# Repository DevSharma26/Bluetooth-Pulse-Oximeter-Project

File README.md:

# EDW-Project
This project is our first ever foray into the world of practical electronics and an attempt to create a working device, Pulse Oximeter (in this case).
All the required info about the components, project specific details plus a beginner's overview is documented in the "project proposal" doc.
The various pointers and our fixes to some common problems are present in the "project documentation".
Also included are the arduino code, the eagle schematic and eagle board layout for the pcb.
This repo contains every piece of info and documentation that we deemed relevant for a third person to understand the motives behind the project and replicate it with elementary knowledge of electronics and pcb fabricating.
However, if any problem is encountered in the project try to troubleshoot using google and/or helpful friends/teachers/professors like we did 
happy bulding!!

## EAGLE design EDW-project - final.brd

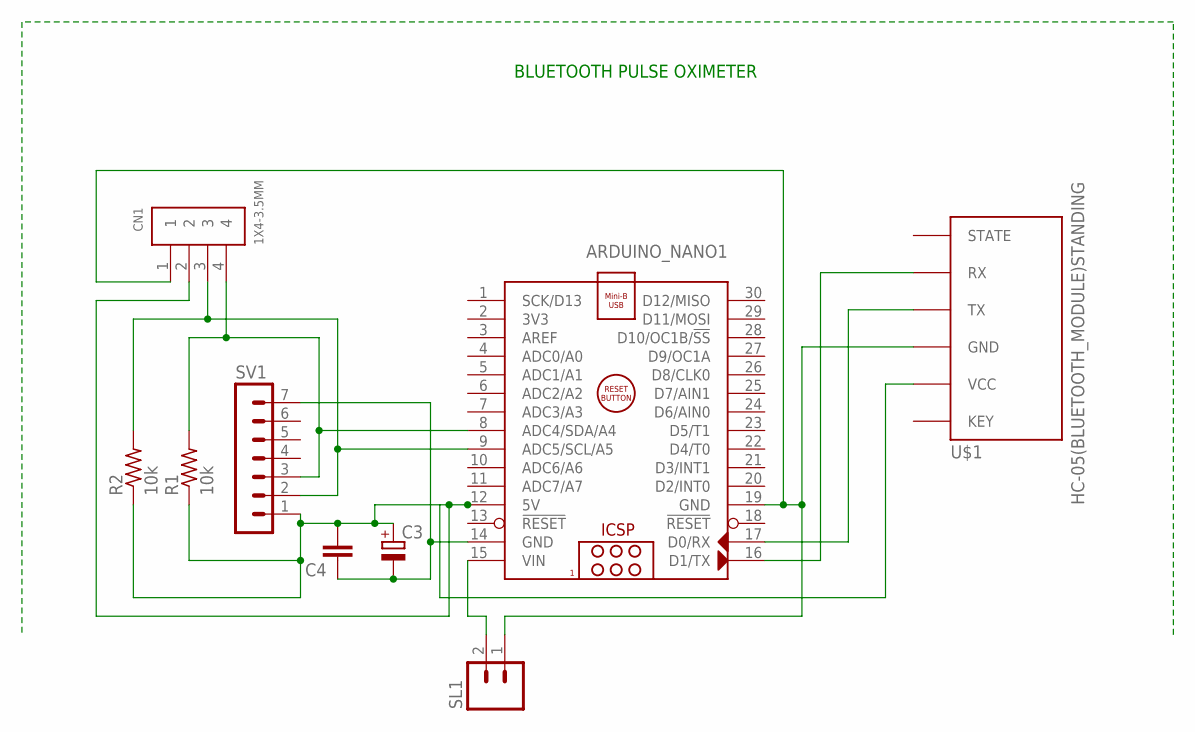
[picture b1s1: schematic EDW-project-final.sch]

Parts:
ARDUINO_NANO1: ARDUINO_NANO
C3: CPOL-EUE2.5-6; E2,5-6
C4: C-EU025-024X044; C025-024X044
CN1: 1X4-3.5MM; 1X04-3.5MM
R1, R2: 10k; 0207/7
SL1: M02; 02P
SV1: MA07-1
U$1: HC-05(BLUETOOTH_MODULE)STANDING; HC-05(STANDING)

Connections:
unnamed: ARDUINO_NANO1.8 (ADC4/SDA/A4), CN1.4, R1.2, SV1.3
unnamed: ARDUINO_NANO1.15 (VIN), SL1.2
unnamed: ARDUINO_NANO1.16 (D1/TX), U$1.RX
unnamed: ARDUINO_NANO1.17 (D0/RX), U$1.TX
unnamed: ARDUINO_NANO1.19 (GND), CN1.1, SL1.1, U$1.GND
unnamed: ARDUINO_NANO1.14 (GND), C3.-, C4.1, SV1.7
unnamed: ARDUINO_NANO1.12 (5V), C3.+, C4.2, CN1.2, R1.1, R2.1, SV1.1, U$1.VCC
unnamed: ARDUINO_NANO1.9 (ADC5/SCL/A5), CN1.3, R2.2, SV1.2

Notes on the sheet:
BLUETOOTH PULSE OXIMETER

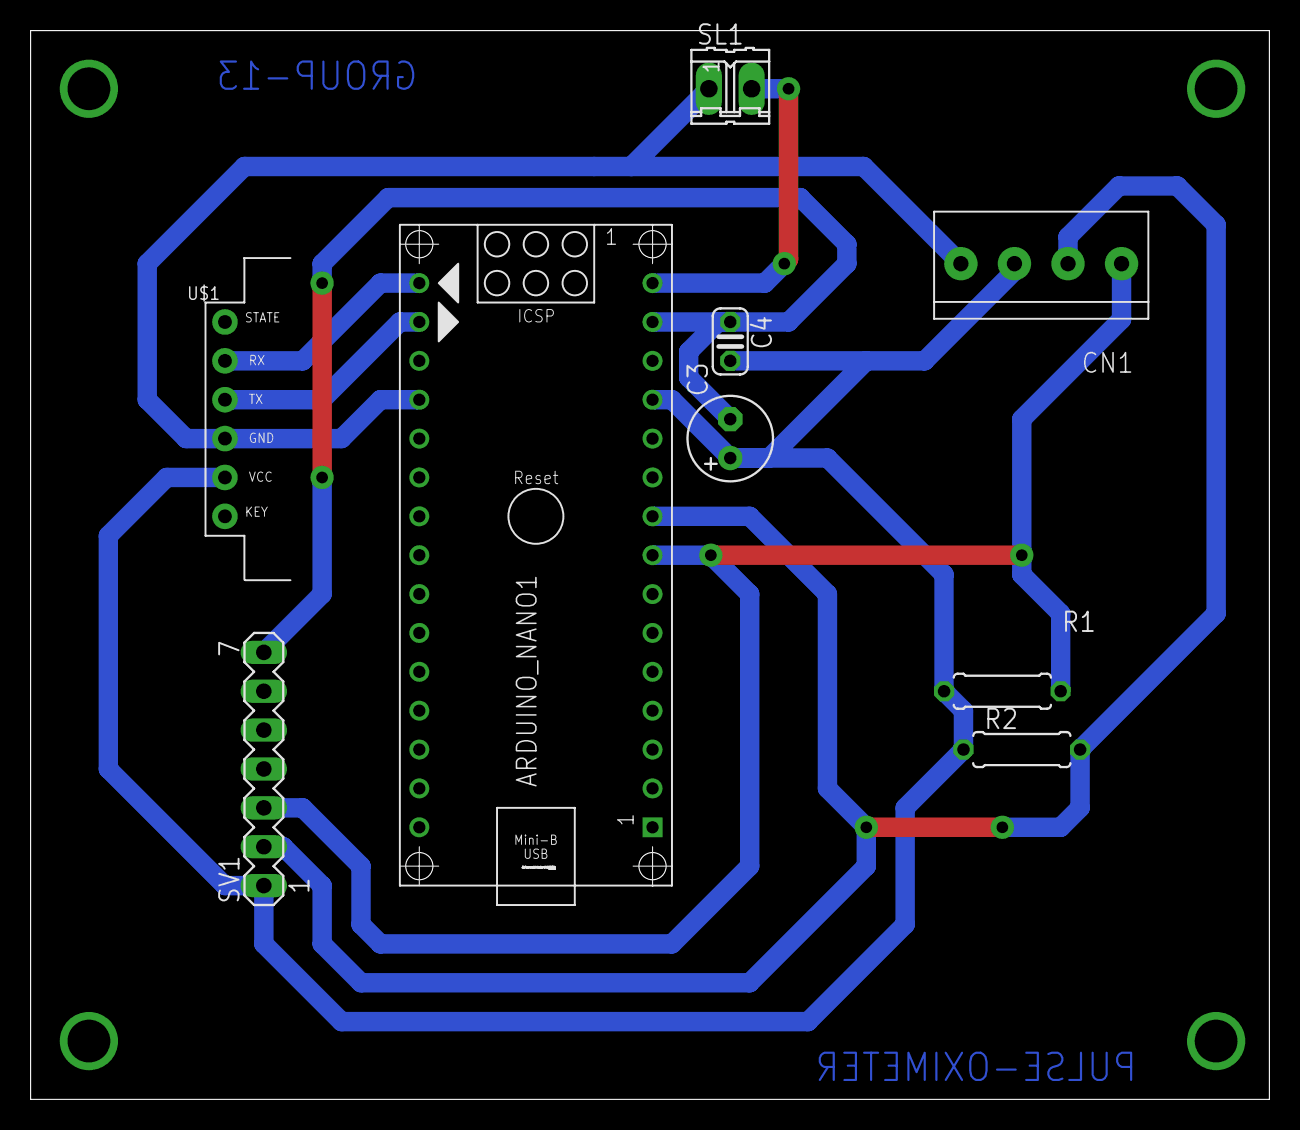
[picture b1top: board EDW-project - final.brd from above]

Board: 2 copper layers, 81.0 x 69.8 mm, 9 parts (0 on the bottom side), 8 nets.
